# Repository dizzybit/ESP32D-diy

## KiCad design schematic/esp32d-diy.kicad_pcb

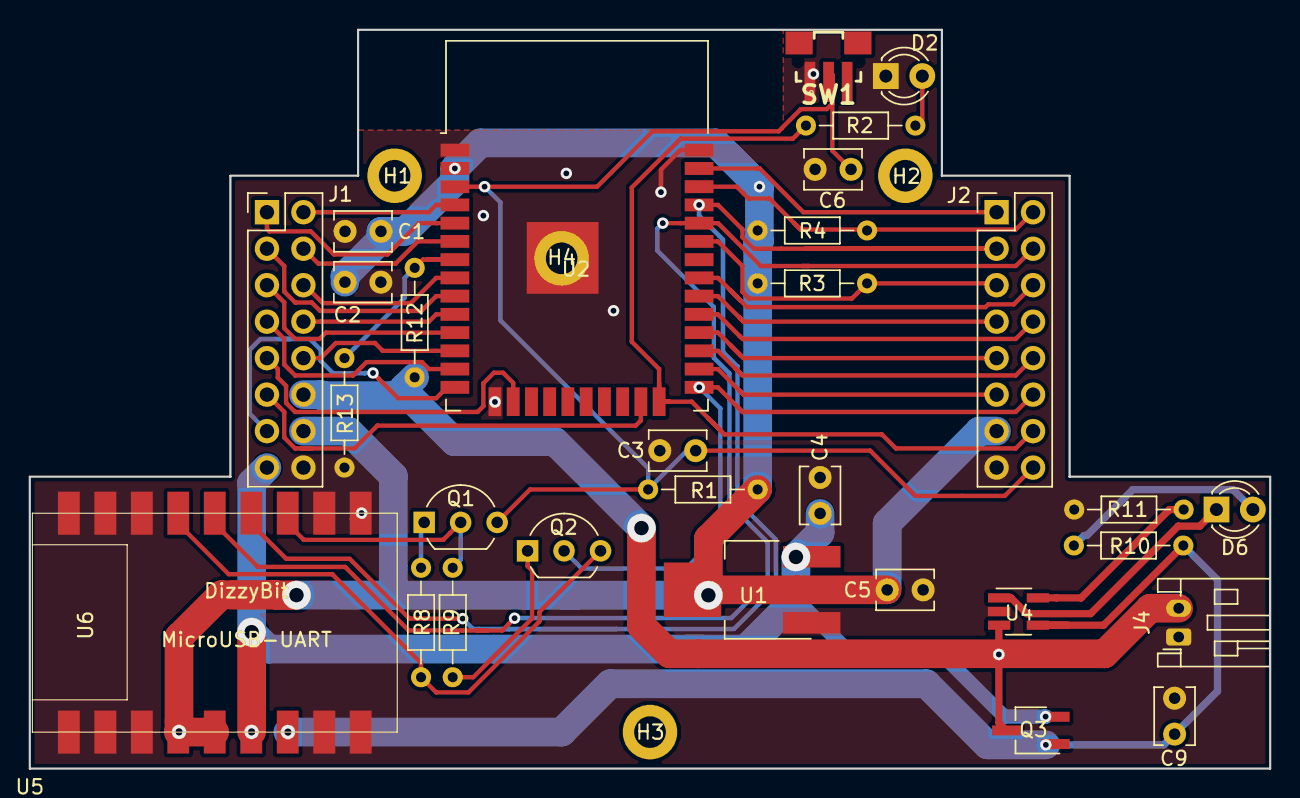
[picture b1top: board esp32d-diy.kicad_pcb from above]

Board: 2 copper layers, 86.4 x 51.4 mm, 36 parts (1 on the bottom side), 40 nets.

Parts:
C1, C3, C6: C0.1uF/50V(10%); C_Disc_D3.8mm_W2.6mm_P2.50mm
C2, C4, C5: C22uF/10V(10%); C_Disc_D3.8mm_W2.6mm_P2.50mm
C9: C4.7uF/6.3V(20%); C_Disc_D3.8mm_W2.6mm_P2.50mm
D2: LED-BLUE; LED_D3.0mm
D6: LED-YELLOW; LED_D3.0mm
H1, H2, H3: MountingHole; MountingHole_2.2mm_M2_DIN965_Pad
H4: MountingHole_Pad; MountingHole_2.2mm_M2_DIN965_Pad
J1, J2: Conn_02x08_Odd_Even; PinHeader_2x08_P2.54mm_Vertical
J4: Conn_01x02; JST_PH_S2B-PH-K_1x02_P2.00mm_Horizontal
Q1, Q2: SS8050DTA; TO-92_Inline_Wide
Q3: DMG2307L-7; SOT-23W_Handsoldering
R1, R8, R9: R10K(5%); R_Axial_DIN0204_L3.6mm_D1.6mm_P7.62mm_Horizontal
R2: R470ohm(1%); R_Axial_DIN0204_L3.6mm_D1.6mm_P7.62mm_Horizontal
R3, R4, R11: R4.7K; R_Axial_DIN0204_L3.6mm_D1.6mm_P7.62mm_Horizontal
R10: R1K; R_Axial_DIN0204_L3.6mm_D1.6mm_P7.62mm_Horizontal
R12, R13: R100K; R_Axial_DIN0204_L3.6mm_D1.6mm_P7.62mm_Horizontal
SW1: SW_Push; TL3340-HandSoldering
U1: AMS1117-3.3; SOT-223-3_TabPin2-HandSoldering
U2: ESP32-WROOM-32D; ESP32-WROOM-32
U3: DizzyBITLogo; DizzyBIT_silk_20
U4: MCP73831-2-OT; SOT-23-5_HandSoldering
U5: DizzyBIT-Layout; DizzyBit-Din Rail Module
U6: DizzyBit-MicroUSB-UART

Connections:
+3.3V: C1.1, C2.1, C5.1, J1.14, J2.13, R1.1, R3.2, R4.2, U1.2, U2.2, U6.13, U6.14
DTR: Q2.3, R8.1, U6.6
EN: C3.1, C6.2, J2.16, Q1.3, R1.2, SW1.2, U2.3
EXT_5V: C4.1, J1.15, Q3.2, U1.3, U6.15
GND: C1.2, C2.2, C3.2, C4.2, C5.2, C6.1, C9.2, D2.1, H4.1, J1.16, J2.15, J4.1, R11.1, R13.2, SW1.1, U1.1, U2.1, U2.15, U2.38, U2.39, U4.2, U6.1, U6.2, U6.7, U6.8, U6.9, U6.10, U6.11, U6.12, U6.17, U6.18
HSPI_CLK: J1.7, U2.13
HSPI_MISO: J1.13, U2.14
HSPI_MOSI: J1.9, U2.16
I2C_SCL: J2.2, R4.1, U2.36
I2C_SDA: J2.5, R3.1, U2.33
I34: J1.4, U2.6
I35: R12.2, R13.1, U2.7
I36: J1.2, U2.4
I39: J1.1, U2.5
IO0: J2.12, Q2.2, U2.25
IO1: J2.3, U2.35, U6.4
IO2: J2.14, R2.1, U2.24
IO3: J2.4, U2.34, U6.5
IO4: J2.11, U2.26
IO5: J2.8, U2.29
IO15: J1.11, U2.23
IO16: J2.10, U2.27
IO17: J2.9, U2.28
IO25: J1.8, U2.10
IO26: J1.5, U2.11
IO27: J1.10, U2.12
IO32: J1.6, U2.8
IO33: J1.3, U2.9
unnamed: D2.2, R2.2
unnamed: D6.1, U4.1
unnamed: D6.2, R10.1
unnamed: Q1.1, R8.2
unnamed: Q2.1, R9.2
unnamed: R11.2, U4.5
RTS: Q1.2, R9.1, U6.3
VBAT: J1.12, J4.2, Q3.3, R12.1, U4.3
VBUS: C9.1, Q3.1, R10.2, U4.4, U6.16
VSPI_CLK: J2.7, U2.30
VSPI_MISO: J2.6, U2.31
VSPI_MOSI: J2.1, U2.37

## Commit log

2019-10-04 Created stand-alone DIY project
